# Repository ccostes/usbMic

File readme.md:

# USB Microphone Interface

This is a DIY USB microphone interface designed for an electret condenser microphone. It has up to 60dB of amplification and 16-bit ADC. This is my first PCB design and this page is intended to document the design itself, as well as my learnings along the way.

The project was created in [KiCad 6](https://www.kicad.org/)

I haven't yet assembled or tested this board, will update when I do.

## Why? 
Mostly as an excuse to design and build a PCB - you can buy something to do the same thing for $10 on Amazon. I'm a software engineer professionally, but did my degree in Electrical and Computer engineering and always wanted to design a board from scratch to feel like a *real engineer*. 😆 Given that, I wouldn't take anything here as authoritative or good practice.

I did go a little over-the-top and design this with probably way more performance and features than necessary, but that's the fun of building things yourself!
## Design Overview
A USB Microphone interface sounds pretty complicated, but luckily there are off-the-shelf components that do everything we need so this design is quite simple with two main components: an amplifier (the little chip) and a USB codec (the big chip).

In case you're unfamiliar with electronic design, component manufacturers publish datasheets for each part that document the part itself but also typically show you an example circuit of how to use it (making it easier to use the parts sells more parts). That means putting together a design like this is mostly an exercise of reading the datasheet carefully and wiring things up the way they show you, but inevitably there are aspects that are left out/unclear/assume you know what you're doing, so things aren't quite *that* simple.

### Amplifier
The first step in building a microphone interface is interfacing with a microphone, which is where the amplifier comes in. I chose the the [MAX9814](https://datasheets.maximintegrated.com/en/ds/MAX9814.pdf), primarily because it has built-in auto-gain-control (AGC) that will decrease the amplification to prevent the output from clipping loud input signals. It has three gain settings that go up to 60dB (which seems like a lot), and provides 2V bias for the microphone. 

[Electret microphones](https://en.wikipedia.org/wiki/Electret_microphone) are actually a combo microphone/amplifier-transistor, and that transistor requires a bias voltage to operate. Check out this [Open Music Labs](http://www.openmusiclabs.com/learning/sensors/electret-microphones/) page for a great explanation of electret microphones.

The amplifier microphone bias is 2V, but some high-performance microphones are rated for 3V, so I've added a 3V bias supply that is connected to the microphone by default, and a optional jumper for the amplifier-supplied 2V. If you want 2V, simply leave the 3V voltage regulator off (of cut the trace) and solder the jumper pads to connect the 2V bias.

### Codec
Once the analog microphone signal is amplified we need to digitize it with an analog-to-digital converter (ADC) and send that over USB in a format that computers recognize. The ADC part isn't too complicated, but USB definitely is, so luckily TI makes the [PCM2906](https://www.ti.com/lit/ds/symlink/pcm2906c.pdf) chip that does all of this (and more)! 

This chip is rather expensive (currently over $12 on [Digikey](https://www.digikey.com/en/products/detail/texas-instruments/PCM2906CDBR/3077993)) and could be replaced by a standalone ADC and microcontroller to reduce cost, but doing so would increase design complexity and require custom software for the USB interface. I might try that as a follow-up design later, but want to keep things simple here which this chip does.

## Schematic
Now that we know the parts involved let's see how everything is wired up! 

Again, most of this comes straight from the "Typical Application Circuit" examples in the datasheets (page 11 in the [MAX datasheet](https://datasheets.maximintegrated.com/en/ds/MAX9814.pdf) and page 24 in the [PCM2906](https://www.ti.com/lit/ds/symlink/pcm2906c.pdf)), so I'll focus on the differences and challenges in going from those to this design.

#### Signal Names:
The first thing to point out is that a lot of the wires in the schematic end with a label. All of the wires with the same labels are connected, and the label meanings are as follows:
* **VBUS**: USB +5V power
* **VCCCI**: analog supply voltage (3.6V) - I will refer to this as Vcc
* ***SSPND**: active-low enable for analog components (0V = enabled)
* **AMPOUT**: amplifier output
* **D+**, **D-**: USB signal lines

Starting with the simple stuff, in the bottom-right Connectors section you see the USB and Microphone connectors, along with an expansion header that brings out power, ground, and the right audio channel.

The top-right is the power-supply section, which takes the (noisy) 5V USB power supply and uses linear voltage regulators to produce 3.6V and 3V. Linear regulators are designed to produce the desired voltage regardless of the input voltage, and whatever difference is wasted as heat. They aren't usually the most efficient (though for a small difference between input and output voltage they can be), but they produce a very smooth output and reject noise that may be on the input supply which is important for the analog audio circuitry here.

### Amplifier

Starting at the top, the shutdown pin (`SHDN` - the line over it means it is inverted logic so logic-low (0V) = shutdown) is wired to the `*SSPND` label (asterisk in place of the bar over the word, same meaning) rather than permanently connected to Vcc as in the datasheet. The `*SSPND` line allows the PCM to power the analog circuitry off when the microphone is not in use.

Moving to the left you can see the positive microphone input line (`MIC+`) is connected through `R1` to both a label `VBIAS` as well as the `MICBIAS` pin of the amplifier through a jumper. As mentioned earlier, this board has both 3V and 2V mic bias supplies. The 3V is on `VBIAS` and is connected by default, and the 2V comes from the amplifier on `MICBIAS` and can be connected by the jumper, being sure to either leave off the 3V regulator or cut the trace. I'm not sure if anything bad would happen if they were both connected, but my guess is the amplifier wouldn't like its bias output to be connected to a higher voltage so I wouldn't recommend that.

Below the microphone lines you'll notice jumper `JP1` between the `GAIN` pin and Vcc. The gain pin configures the maximum gain of the amplifier. Unconnected = 60dB, Ground = 50dB, and Vcc = 40dB. By default I have it unconnected to get the full 60dB range, but I thought that might be too much so added a solder jumper to allow that to be reduced to 40dB.

The amplifier output is on the right which goes to the `AMPOUT` label.

### Codec

The main aspect of the codec I struggled with was how to connect the amplifier output - whether I could just connect them directly or if I needed some sort of matching circuitry. As you can see in the schematic, I only have a coupling capacitor between the two, which removes the bias voltage from the amplifier output and results in a 0V center voltage.

The MAX datasheet specifies that its output has a center-voltage of 1.23V which could be removed by placing a coupling capacitor in series. The PCM datasheet "Analog Input" section specified a center-voltage of Vcc/2, so I though that I needed to shift the output up by about 0.7V. Confusingly, the PCM datasheet example application ony showed coupling capacitors in front of the inputs - indicating 0V input bias.

I [asked](https://www.reddit.com/r/AskElectronics/comments/sm6ebf/audio_adc_input_bias/) on reddit and a couple people pointed out that the block diagram of the Analog frontend shows that the input is internally biased, so needed a 0V center voltage and all I needed was the coupling capacitor as the schematic showed. I still think the Analog Input section should have specified 0V instead of Vcc/2 center voltage.

## PCB Layout
Full layout

Front Copper

Back Copper

This layout went though a number of revisions and I learned a lot along the way. Making my own part footprints turned out to be really important. Some parts didn't have footprints available online, and even those that do should be inspected to make sure they actually match the datasheet.

I found the routing to be pretty difficult with KiCad (unsure if it's like this in all programs) because you can't 'move' the tra ces once you draw them, so rearranging things is quite time-consuming.

The board is almost single-sided; there were two power traces I put on the back side. I probably could have made a lot more use of the back side, but for some reason tried to minimize vias. 

All parts other than the crystal are surface-mount (SMD), and I went with 0603 size resistors/capacitors. I've never constructed a PCB with components this small, so that will be another learning experience for sure. My plan is to hotplate reflow solder the surface-mount components.

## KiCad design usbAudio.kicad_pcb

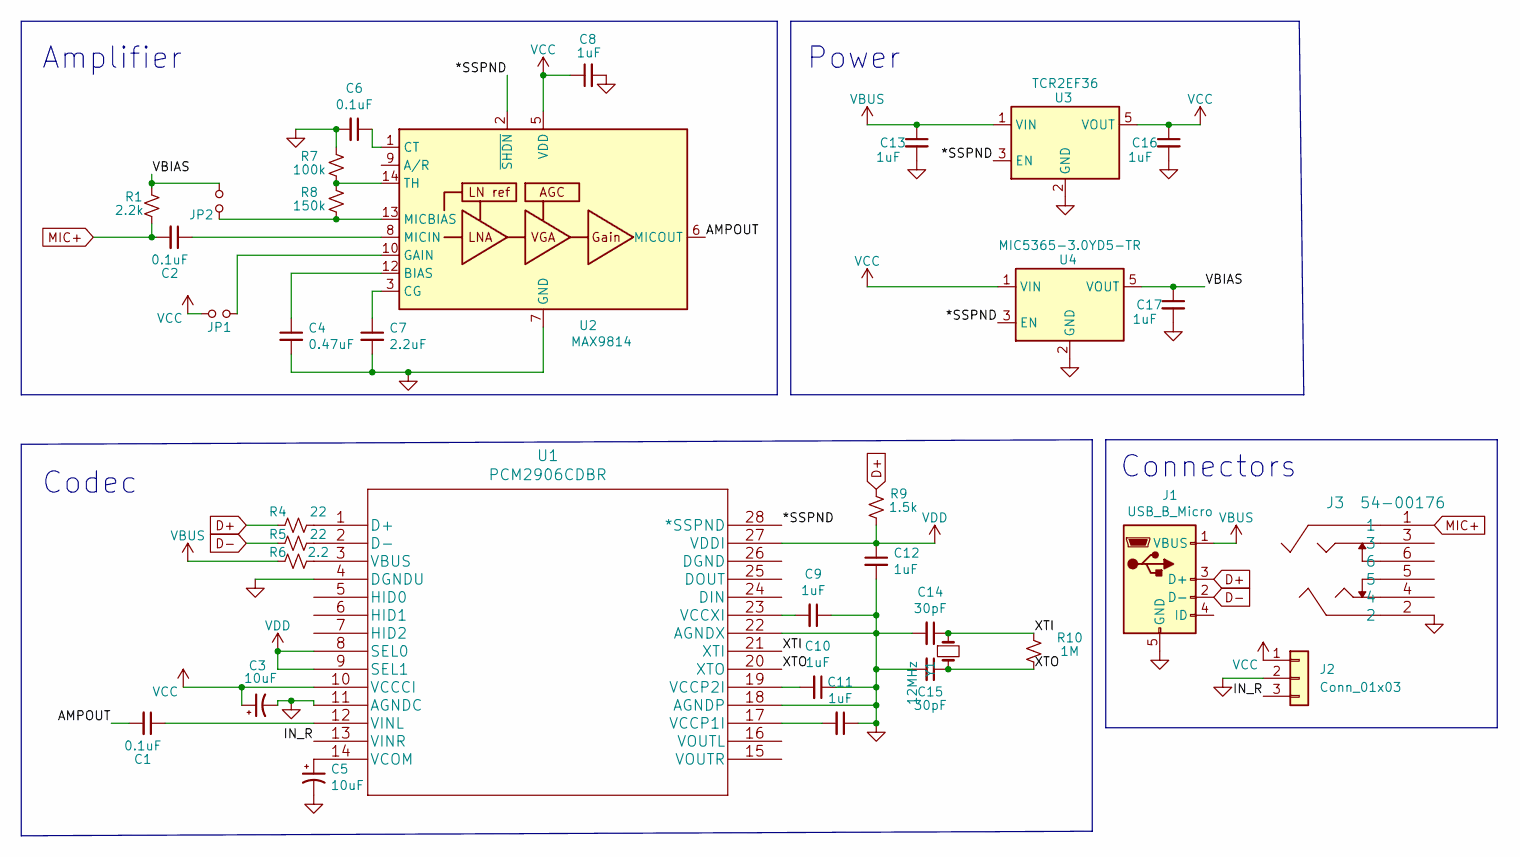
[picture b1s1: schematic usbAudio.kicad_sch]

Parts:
C1, C2, C6: 0.1uF; C_0603_1608Metric_Pad1.08x0.95mm_HandSolder
C3, C5: 10uF; C_1206_3216Metric_Pad1.33x1.80mm_HandSolder
C4: 0.47uF; C_0603_1608Metric_Pad1.08x0.95mm_HandSolder
C7: 2.2uF; C_0603_1608Metric_Pad1.08x0.95mm_HandSolder
C8, C9, C10, C11, C12, C13, C16, C17: 1uF; C_0603_1608Metric_Pad1.08x0.95mm_HandSolder
C14, C15: 30pF; C_0603_1608Metric_Pad1.08x0.95mm_HandSolder
J1: USB_B_Micro; 10118194-0001LF
J2: Conn_01x03; TO-92Flat
J3: 54-00176; 54-00177
JP1, JP2: Jumper_NO_Small; SolderJumper-2_P1.3mm_Open_RoundedPad1.0x1.5mm
R1: 2.2k; R_0603_1608Metric_Pad0.98x0.95mm_HandSolder
R4, R5: 22; R_0603_1608Metric_Pad0.98x0.95mm_HandSolder
R6: 2.2; R_0603_1608Metric_Pad0.98x0.95mm_HandSolder
R7: 100k; R_0603_1608Metric_Pad0.98x0.95mm_HandSolder
R8: 150k; R_0603_1608Metric_Pad0.98x0.95mm_HandSolder
R9: 1.5k; R_0603_1608Metric_Pad0.98x0.95mm_HandSolder
R10: 1M; R_0603_1608Metric_Pad0.98x0.95mm_HandSolder
U1: PCM2906CDBR
U2: MAX9814; max9814etd&plus_t
U3: TCR2EF36; SOT-23-5
U4: MIC5365-3.0YD5-TR; SOT-23-5
Y1: 12MHz; Crystal_SMD_5032-4Pin_5.0x3.2mm

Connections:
/*SSPND: U1.28 (*SSPND), U2.2 (~SHDN), U3.3 (EN), U4.3 (EN)
/AMPOUT: C1.2, U2.6 (MICOUT)
/IN_R: J2.3, U1.13 (VINR)
/VBIAS: C17.1, JP2.2, R1.1, U4.5 (VOUT)
/XTI: C14.1, R10.2, U1.21 (XTI), Y1.1
/XTO: C15.1, R10.1, U1.20 (XTO), Y1.3
D+: J1.3 (D+), R4.2, R9.2
D-: J1.2 (D-), R5.2
GND: C3.2, C4.2, C5.2, C6.2, C7.2, C8.2, C9.1, C10.1, C11.1, C12.2, C13.2, C14.2, C15.2, C16.2, C17.2, J1.5 (GND), J2.2, J3.2, R7.2, U1.4 (DGNDU), U1.11 (AGNDC), U1.18 (AGNDP), U1.22 (AGNDX), U2.4 (GND), U2.7 (GND), U2.11 (GND), U2.15 (GND), U3.2 (GND), U4.2 (GND)
MIC+: C2.2, J3.1, R1.2
unnamed: C1.1, U1.12 (VINL)
unnamed: C2.1, U2.8 (MICIN)
unnamed: C4.1, U2.12 (BIAS)
unnamed: C5.1, U1.14 (VCOM)
unnamed: C6.1, U2.1 (CT)
unnamed: C7.1, U2.3 (CG)
unnamed: C9.2, U1.23 (VCCXI)
unnamed: C10.2, U1.19 (VCCP2I)
unnamed: C11.2, U1.17 (VCCP1I)
unnamed: JP1.2, U2.10 (GAIN)
unnamed: JP2.1, R8.1, U2.13 (MICBIAS)
unnamed: R4.1, U1.1 (D+)
unnamed: R5.1, U1.2 (D-)
unnamed: R6.1, U1.3 (VBUS)
unnamed: R7.1, R8.2, U2.14 (TH)
VBUS: C13.1, J1.1 (VBUS), R6.2, U3.1 (VIN)
VCC: C3.1, C8.1, C16.1, J2.1, JP1.1, U1.10 (VCCCI), U2.5 (VDD), U3.5 (VOUT), U4.1 (VIN)
VDD: C12.1, R9.1, U1.8 (SEL0), U1.9 (SEL1), U1.27 (VDDI)

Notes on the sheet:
Connectors
Power
Codec
Amplifier

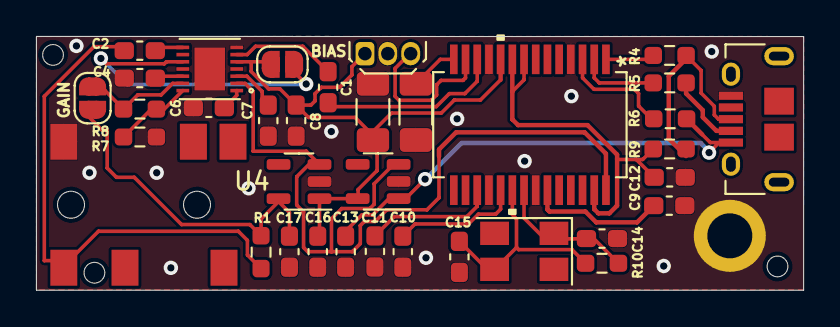
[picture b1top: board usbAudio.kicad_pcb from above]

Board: 2 copper layers, 42.6 x 14.1 mm, 37 parts (0 on the bottom side), 28 nets.

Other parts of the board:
ALIGN1, ALIGN2: MountingHole_2.1mm

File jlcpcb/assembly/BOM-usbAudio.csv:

Comment,Designator,Footprint,LCSC
USB_B_Micro,J1,10118194-0001LF,C132563
10uF,"C3,C5",C_1206_3216Metric_Pad1.33x1.80mm_HandSolder,C13585
0.1uF,"C1,C2,C6",C_0603_1608Metric_Pad1.08x0.95mm_HandSolder,C14858
1uF,"C10,C11,C12,C13,C16,C17,C8,C9",C_0603_1608Metric_Pad1.08x0.95mm_HandSolder,C15849
0.47uF,C4,C_0603_1608Metric_Pad1.08x0.95mm_HandSolder,C19666
30pF,"C14,C15",C_0603_1608Metric_Pad1.08x0.95mm_HandSolder,C22397
150k,R8,R_0603_1608Metric_Pad0.98x0.95mm_HandSolder,C22807
1.5k,R9,R_0603_1608Metric_Pad0.98x0.95mm_HandSolder,C22843
1M,R10,R_0603_1608Metric_Pad0.98x0.95mm_HandSolder,C22935
2.2,R6,R_0603_1608Metric_Pad0.98x0.95mm_HandSolder,C22939
22,"R4,R5",R_0603_1608Metric_Pad0.98x0.95mm_HandSolder,C23345
2.2uF,C7,C_0603_1608Metric_Pad1.08x0.95mm_HandSolder,C23630
100k,R7,R_0603_1608Metric_Pad0.98x0.95mm_HandSolder,C25803
12MHz,Y1,Crystal_SMD_5032-4Pin_5.0x3.2mm,C390782
2.2k,R1,R_0603_1608Metric_Pad0.98x0.95mm_HandSolder,C4190
PCM2906CDBR,U1,PCM2906CDBR,
MAX9814,U2,max9814etd&plus_t,
54-00176,J3,54-00177,
Jumper_NO_Small,JP1,SolderJumper-2_P1.3mm_Open_RoundedPad1.0x1.5mm,
Conn_01x03,J2,TO-92Flat,
Jumper_NO_Small,JP2,SolderJumper-2_P1.3mm_Open_RoundedPad1.0x1.5mm,
TCR2EF36,U3,SOT-23-5,
MIC5365-3.0YD5-TR,U4,SOT-23-5,

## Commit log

2022-02-09 Update design and readme
2022-02-09 Updates from reddit feedback https://www.reddit.com/r/PrintedCircuitBoard/comments/so21cn/project_review_usb_microphone_interface/
2022-02-13 Changes for JLC production. Add mounting hole.
2022-02-13 Fix crystal pin mappings (1 and 3 instead of 1 and 2)

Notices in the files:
parts and their libraries:
Copyright 2021 Accelerated Designs. All rights reserved.
